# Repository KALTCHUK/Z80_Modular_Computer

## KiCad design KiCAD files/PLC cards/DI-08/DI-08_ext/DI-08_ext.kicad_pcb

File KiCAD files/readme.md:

## What you'll find in this directory ##
The most important here are the two directories called "Proton cards" and "PLC cards", which contain respectively all the cards used in the Proton projects and, all the I/O cards mounted on DIN rail, which communicate with the Proton via Modbus protocol over RS485.

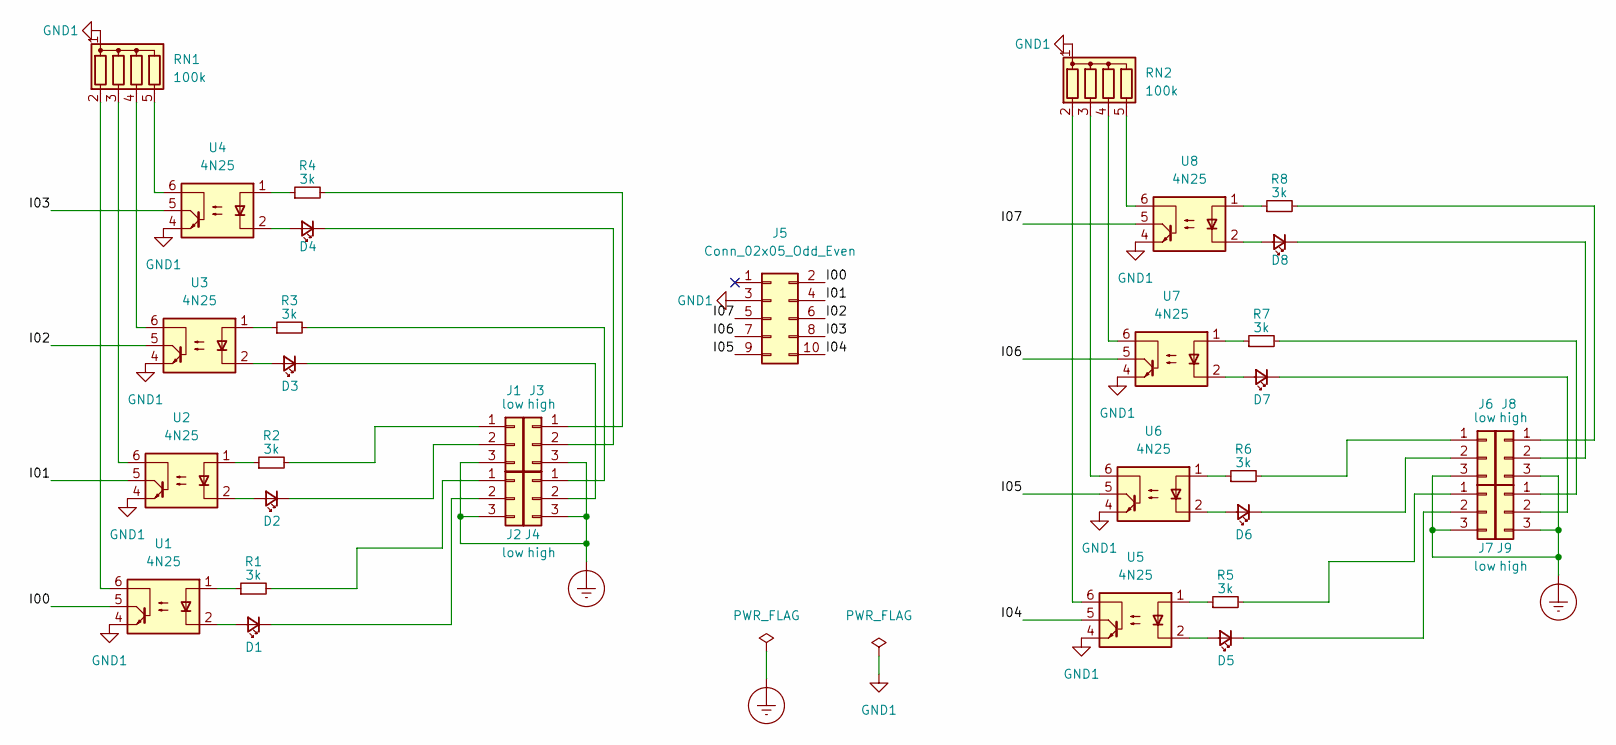
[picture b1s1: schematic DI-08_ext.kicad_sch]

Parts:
D1, D2, D3, D4, D5, D6, D7, D8: LED_Small; LED_D3.0mm
J1, J2, J6, J7: low; PhoenixContact_MSTBVA_2,5_3-G-5,08_1x03_P5.08mm_Vertical
J3, J4, J8, J9: high; PhoenixContact_MSTBVA_2,5_3-G-5,08_1x03_P5.08mm_Vertical
J5: Conn_02x05_Odd_Even; PinSocket_2x05_P2.54mm_Vertical
R1, R2, R3, R4, R5, R6, R7, R8: 3k; R_Axial_DIN0207_L6.3mm_D2.5mm_P2.54mm_Vertical
RN1, RN2: 100k; R_Array_SIP5
U1, U2, U3, U4, U5, U6, U7, U8: 4N25; DIP-6_W7.62mm_Socket_LongPads

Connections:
/I00: J5.2, U1.5
/I01: J5.4, U2.5
/I02: J5.6, U3.5
/I03: J5.8, U4.5
/I04: J5.10, U5.5
/I05: J5.9, U6.5
/I06: J5.7, U7.5
/I07: J5.5, U8.5
Earth_Protective: J1.3, J2.3, J3.3, J4.3, J6.3, J7.3, J8.3, J9.3
GND1: J5.3, RN1.1 (common), RN2.1 (common), U1.4, U2.4, U3.4, U4.4, U5.4, U6.4, U7.4, U8.4
unnamed: D1.1 (K), J2.2
unnamed: D1.2 (A), U1.2
unnamed: D2.1 (K), J1.2
unnamed: D2.2 (A), U2.2
unnamed: D3.1 (K), J4.2
unnamed: D3.2 (A), U3.2
unnamed: D4.1 (K), J3.2
unnamed: D4.2 (A), U4.2
unnamed: D5.1 (K), J7.2
unnamed: D5.2 (A), U5.2
unnamed: D6.1 (K), J6.2
unnamed: D6.2 (A), U6.2
unnamed: D7.1 (K), J9.2
unnamed: D7.2 (A), U7.2
unnamed: D8.1 (K), J8.2
unnamed: D8.2 (A), U8.2
unnamed: J1.1, R2.2
unnamed: J2.1, R1.2
unnamed: J3.1, R4.2
unnamed: J4.1, R3.2
unnamed: J6.1, R6.2
unnamed: J7.1, R5.2
unnamed: J8.1, R8.2
unnamed: J9.1, R7.2
unnamed: R1.1, U1.1
unnamed: R2.1, U2.1
unnamed: R3.1, U3.1
unnamed: R4.1, U4.1
unnamed: R5.1, U5.1
unnamed: R6.1, U6.1
unnamed: R7.1, U7.1
unnamed: R8.1, U8.1
unnamed: RN1.2 (R1), U1.6
unnamed: RN1.3 (R2), U2.6
unnamed: RN1.4 (R3), U3.6
unnamed: RN1.5 (R4), U4.6
unnamed: RN2.2 (R1), U5.6
unnamed: RN2.3 (R2), U6.6
unnamed: RN2.4 (R3), U7.6
unnamed: RN2.5 (R4), U8.6

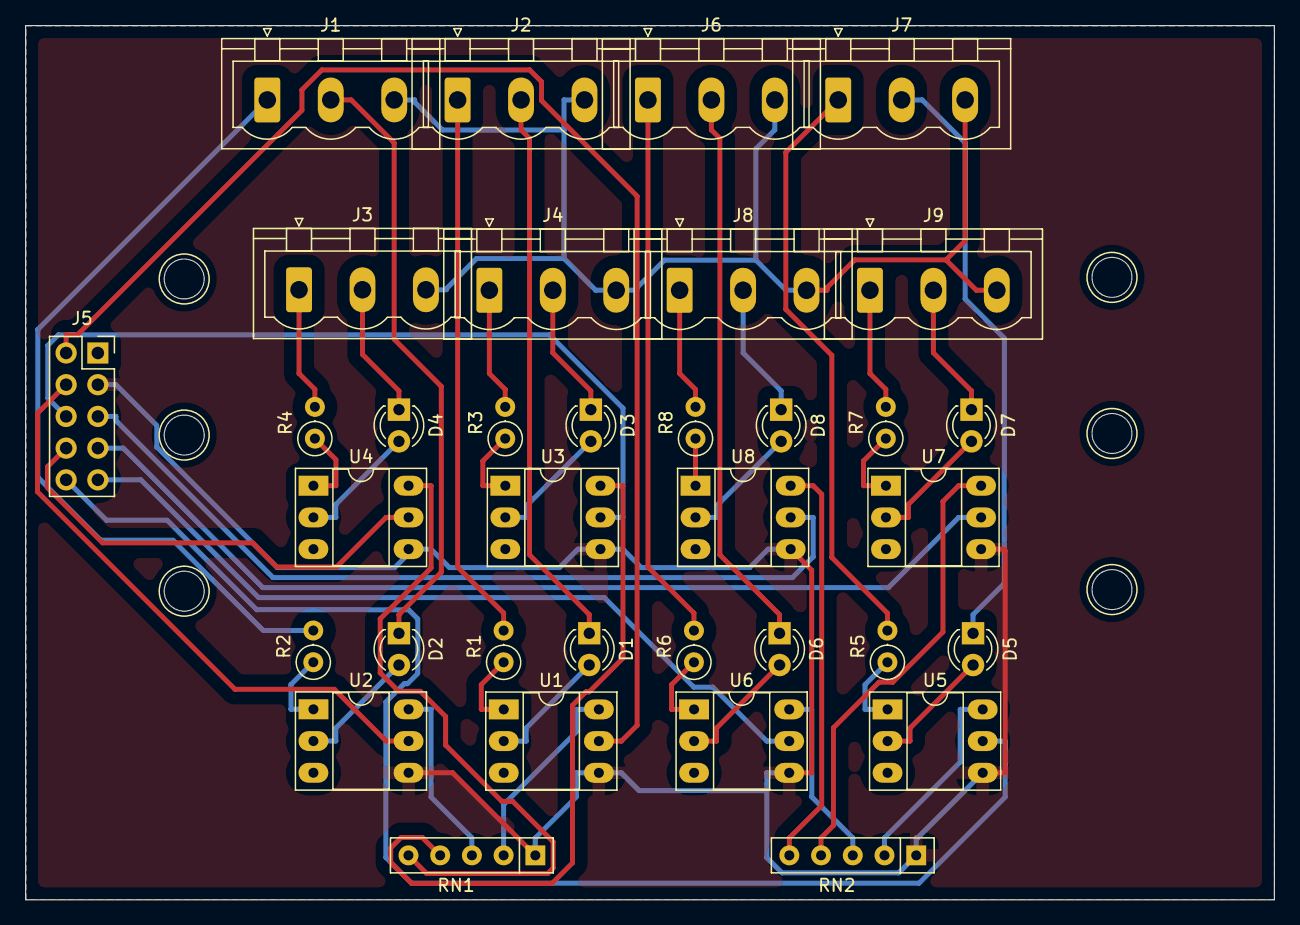
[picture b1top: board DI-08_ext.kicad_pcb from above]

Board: 2 copper layers, 100.0 x 70.0 mm, 37 parts (0 on the bottom side), 50 nets.

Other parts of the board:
DRA1, DRA2: DIN_Rail_Adapter; DINRailAdapter_3xM3_PhoenixContact_1201578

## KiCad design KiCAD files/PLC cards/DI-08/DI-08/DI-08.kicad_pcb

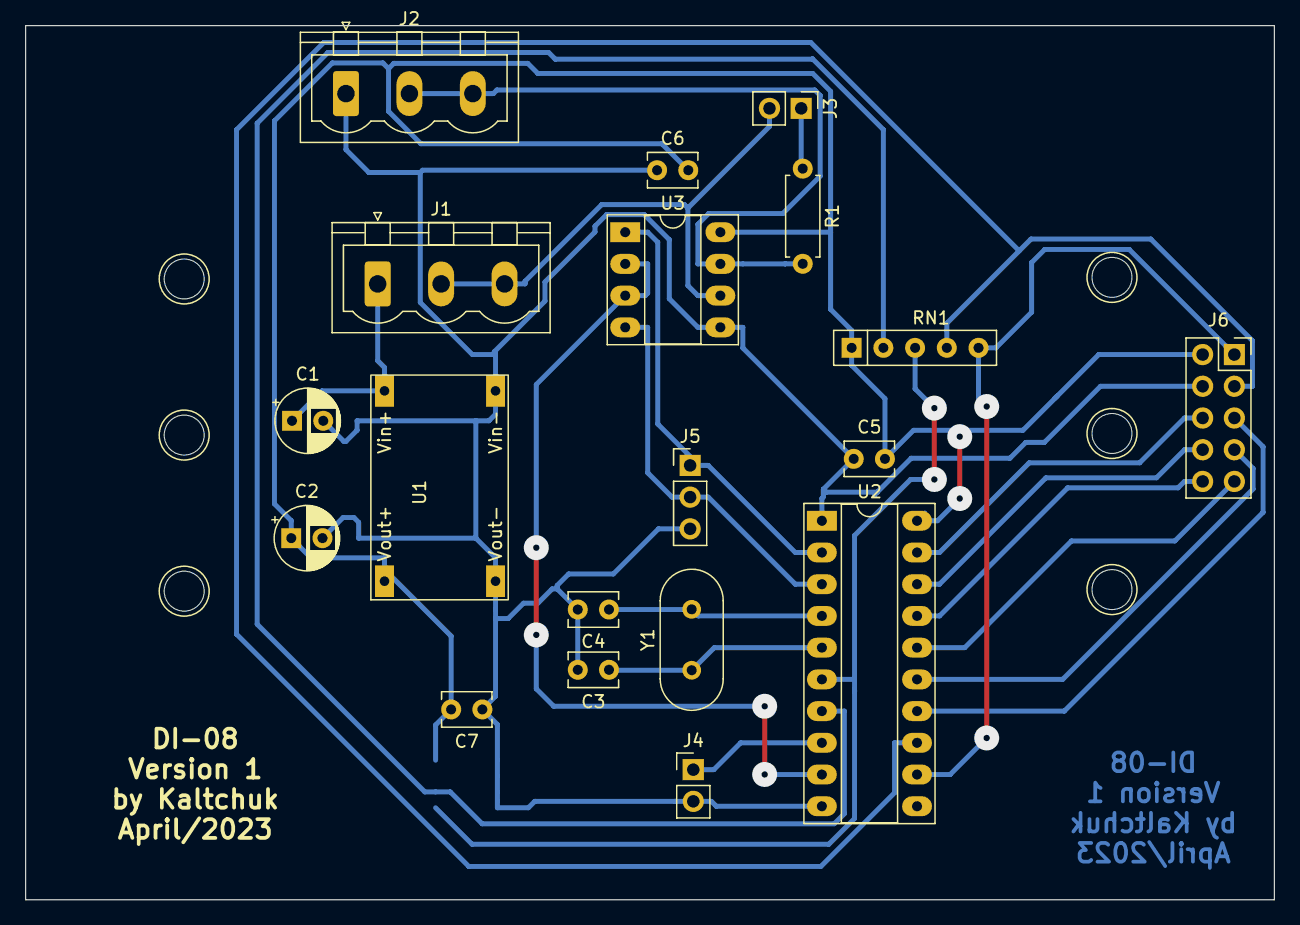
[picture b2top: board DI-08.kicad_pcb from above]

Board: 2 copper layers, 100.0 x 70.0 mm, 22 parts (1 on the bottom side), 22 nets.

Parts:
C1: 47uF; CP_Radial_D5.0mm_P2.50mm
C2: 22uF; CP_Radial_D5.0mm_P2.50mm
C3, C4: 33pF; C_Disc_D3.8mm_W2.6mm_P2.50mm
C5, C6, C7: 10nF; C_Disc_D3.8mm_W2.6mm_P2.50mm
DRA1, DRA2: DIN_Rail_Adapter; DINRailAdapter_3xM3_PhoenixContact_1201578
J1: high; PhoenixContact_MSTBVA_2,5_3-G-5,08_1x03_P5.08mm_Vertical
J2: low; PhoenixContact_MSTBVA_2,5_3-G-5,08_1x03_P5.08mm_Vertical
J3: terminal; PinHeader_1x02_P2.54mm_Vertical
J4: factory setup; PinHeader_1x02_P2.54mm_Vertical
J5: TTL comm; PinHeader_1x03_P2.54mm_Vertical
J6: Bridge_female; PinSocket_2x05_P2.54mm_Vertical
R1: 250; R_Axial_DIN0207_L6.3mm_D2.5mm_P7.62mm_Horizontal
RN1: 10k; R_Array_SIP5
U1: DSN-MINI-360
U2: AT89C4051-24P; DIP-20_W7.62mm_Socket_LongPads
U3: SN75176AP; DIP-8_W7.62mm_Socket_LongPads
U4: FM24C64B; SOIC-8_3.9x4.9mm_P1.27mm
Y1: 11.059MHz; Crystal_HC49-U_Vertical

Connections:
+5V: C2.1, C5.2, C6.2, C7.2, J6.2, RN1.1 (common), U1.1 (Vout+), U2.20 (VCC), U3.8 (VCC), U4.8 (VDD)
+24V: C1.1, J1.1, U1.3 (Vin+)
/DE: U2.9 (P3.5), U3.2 (~RE), U3.3 (DE)
/FS: J4.1, U2.8 (P3.4)
/MB-A: J1.2, J1.3, J3.2, U3.6 (A)
/MB-B: J2.2, J2.3, R1.2, U3.7 (B)
/RX: J5.1, U2.2 (P3.0), U3.1 (R)
/SCL: RN1.2 (R1), U2.7 (P3.3), U4.6 (SCL)
/SDA: RN1.3 (R2), U2.6 (P3.2), U4.5 (SDA)
/TX: J5.2, U2.3 (P3.1), U3.4 (D)
GND: C1.2, C2.2, C3.2, C4.2, C5.1, C6.1, C7.1, J2.1, J4.2, J5.3, J6.4, U1.2 (Vout-), U1.4 (Vin-), U2.1 (RST/VPP), U2.10 (GND), U3.5 (GND), U4.1 (A0), U4.2 (A1), U4.3 (A2), U4.4 (VSS)
unnamed: C3.1, U2.5 (XTAL1), Y1.1
unnamed: C4.1, U2.4 (XTAL2), Y1.2
unnamed: J3.1, R1.1
unnamed: J6.1, RN1.5 (R4), U2.12 (P1.0)
unnamed: J6.3, RN1.4 (R3), U2.13 (P1.1)
unnamed: J6.5, U2.14 (P1.2)
unnamed: J6.6, U2.19 (P1.7)
unnamed: J6.7, U2.15 (P1.3)
unnamed: J6.8, U2.18 (P1.6)
unnamed: J6.9, U2.16 (P1.4)
unnamed: J6.10, U2.17 (P1.5)

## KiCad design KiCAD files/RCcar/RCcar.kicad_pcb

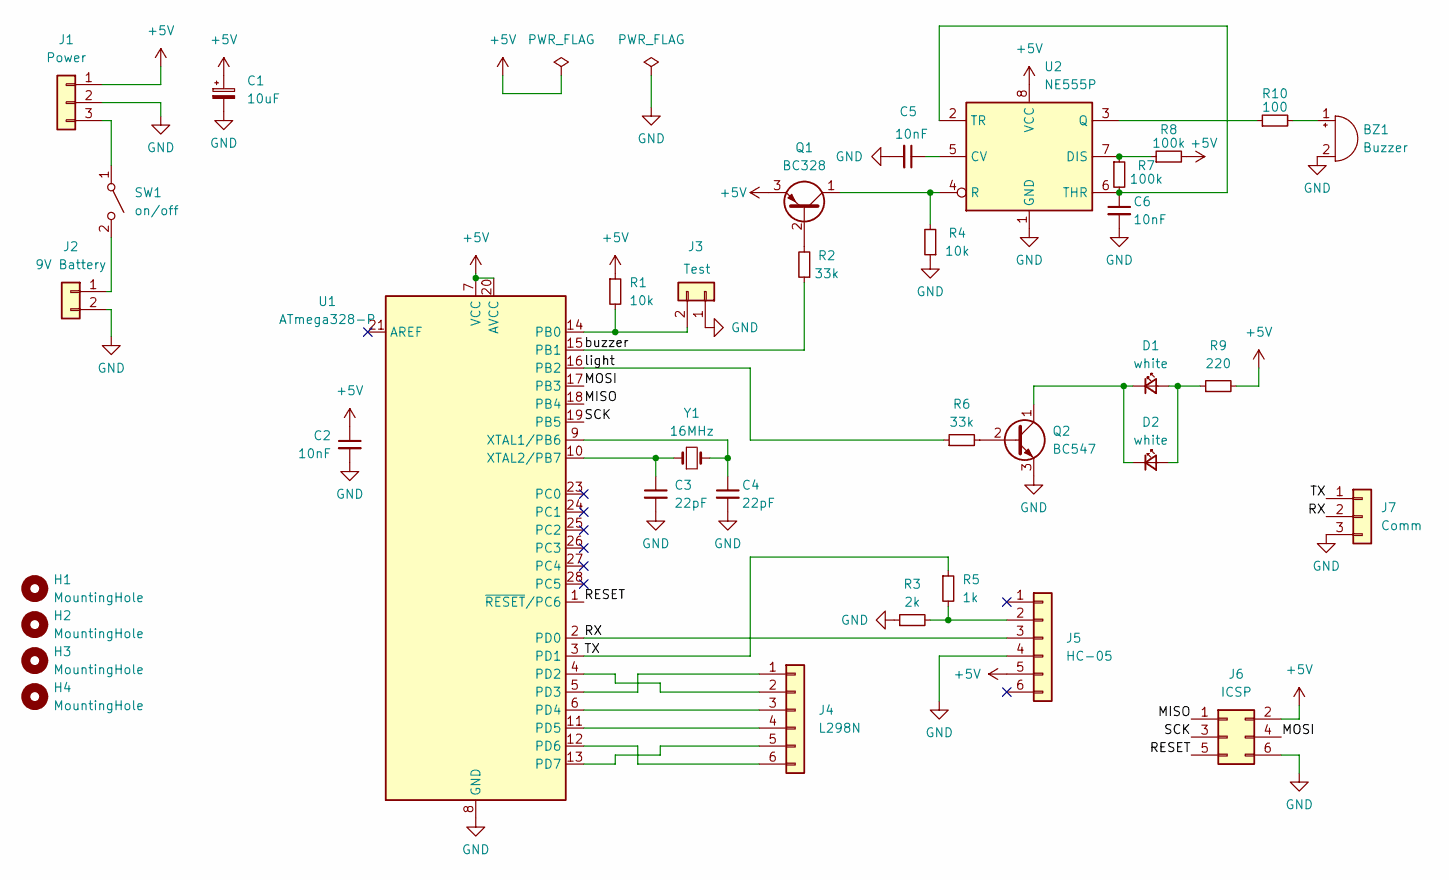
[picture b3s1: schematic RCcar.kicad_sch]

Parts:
BZ1: Buzzer; Buzzer_12x9.5RM7.6
C1: 10uF; CP_Radial_D5.0mm_P2.50mm
C2, C5, C6: 10nF; C_Disc_D3.0mm_W2.0mm_P2.50mm
C3, C4: 22pF; C_Disc_D3.0mm_W2.0mm_P2.50mm
D1, D2: white; LED_D3.0mm_Clear
H1, H2, H3, H4: MountingHole; MountingHole_3mm
J1: Power; PinHeader_1x03_P2.54mm_Vertical
J2: 9V Battery; PinHeader_1x02_P2.54mm_Vertical
J3: Test; PinHeader_1x02_P2.54mm_Vertical
J4: L298N; PinHeader_1x06_P2.54mm_Vertical
J5: HC-05; PinSocket_1x06_P2.54mm_Vertical
J6: ICSP; PinHeader_2x03_P2.54mm_Vertical
J7: Comm; PinHeader_1x03_P2.54mm_Vertical
Q1: BC328; TO-92_Inline
Q2: BC547; TO-92_Inline
R1, R4: 10k; R_Axial_DIN0207_L6.3mm_D2.5mm_P7.62mm_Horizontal
R2, R6: 33k; R_Axial_DIN0207_L6.3mm_D2.5mm_P7.62mm_Horizontal
R3: 2k; R_Axial_DIN0207_L6.3mm_D2.5mm_P7.62mm_Horizontal
R5: 1k; R_Axial_DIN0207_L6.3mm_D2.5mm_P7.62mm_Horizontal
R7, R8: 100k; R_Axial_DIN0207_L6.3mm_D2.5mm_P7.62mm_Horizontal
R9: 220; R_Axial_DIN0207_L6.3mm_D2.5mm_P7.62mm_Horizontal
R10: 100; R_Axial_DIN0207_L6.3mm_D2.5mm_P7.62mm_Horizontal
SW1: on/off; SW_CW_GPTS203211B
U1: ATmega328-P; DIP-28_W7.62mm_Socket_LongPads
U2: NE555P; DIP-8_W7.62mm_Socket_LongPads
Y1: 16MHz; Crystal_HC49-4H_Vertical

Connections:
+5V: C1.1, C2.1, J1.1, J5.5, J6.2, Q1.3 (E), R1.1, R8.2, R9.2, U1.7 (VCC), U1.20 (AVCC), U2.8 (VCC)
/MISO: J6.1, U1.18 (PB4)
/MOSI: J6.4, U1.17 (PB3)
/RESET: J6.5, U1.1 (~RESET/PC6)
/RX: J5.3, J7.2, U1.2 (PD0)
/SCK: J6.3, U1.19 (PB5)
/TX: J7.1, R5.1, U1.3 (PD1)
/buzzer: R2.1, U1.15 (PB1)
/light: R6.1, U1.16 (PB2)
GND: BZ1.2 (+), C1.2, C2.2, C3.2, C4.2, C5.2, C6.2, J1.2, J2.2, J3.1, J5.4, J6.6, J7.3, Q2.3 (E), R3.1, R4.1, U1.8 (GND), U1.22 (GND), U2.1 (GND)
unnamed: BZ1.1 (-), R10.2
unnamed: C3.1, U1.10 (XTAL2/PB7), Y1.1
unnamed: C4.1, U1.9 (XTAL1/PB6), Y1.2
unnamed: C5.1, U2.5 (CV)
unnamed: C6.1, R7.2, U2.2 (TR), U2.6 (THR)
unnamed: D1.1 (K), D2.1 (K), Q2.1 (C)
unnamed: D1.2 (A), D2.2 (A), R9.1
unnamed: J1.3, SW1.1 (A)
unnamed: J2.1, SW1.2 (B)
unnamed: J3.2, R1.2, U1.14 (PB0)
unnamed: J4.1, U1.5 (PD3)
unnamed: J4.2, U1.4 (PD2)
unnamed: J4.3, U1.6 (PD4)
unnamed: J4.4, U1.11 (PD5)
unnamed: J4.5, U1.13 (PD7)
unnamed: J4.6, U1.12 (PD6)
unnamed: J5.2, R3.2, R5.2
unnamed: Q1.1 (C), R4.2, U2.4 (R)
unnamed: Q1.2 (B), R2.2
unnamed: Q2.2 (B), R6.2
unnamed: R7.1, R8.1, U2.7 (DIS)
unnamed: R10.1, U2.3 (Q)

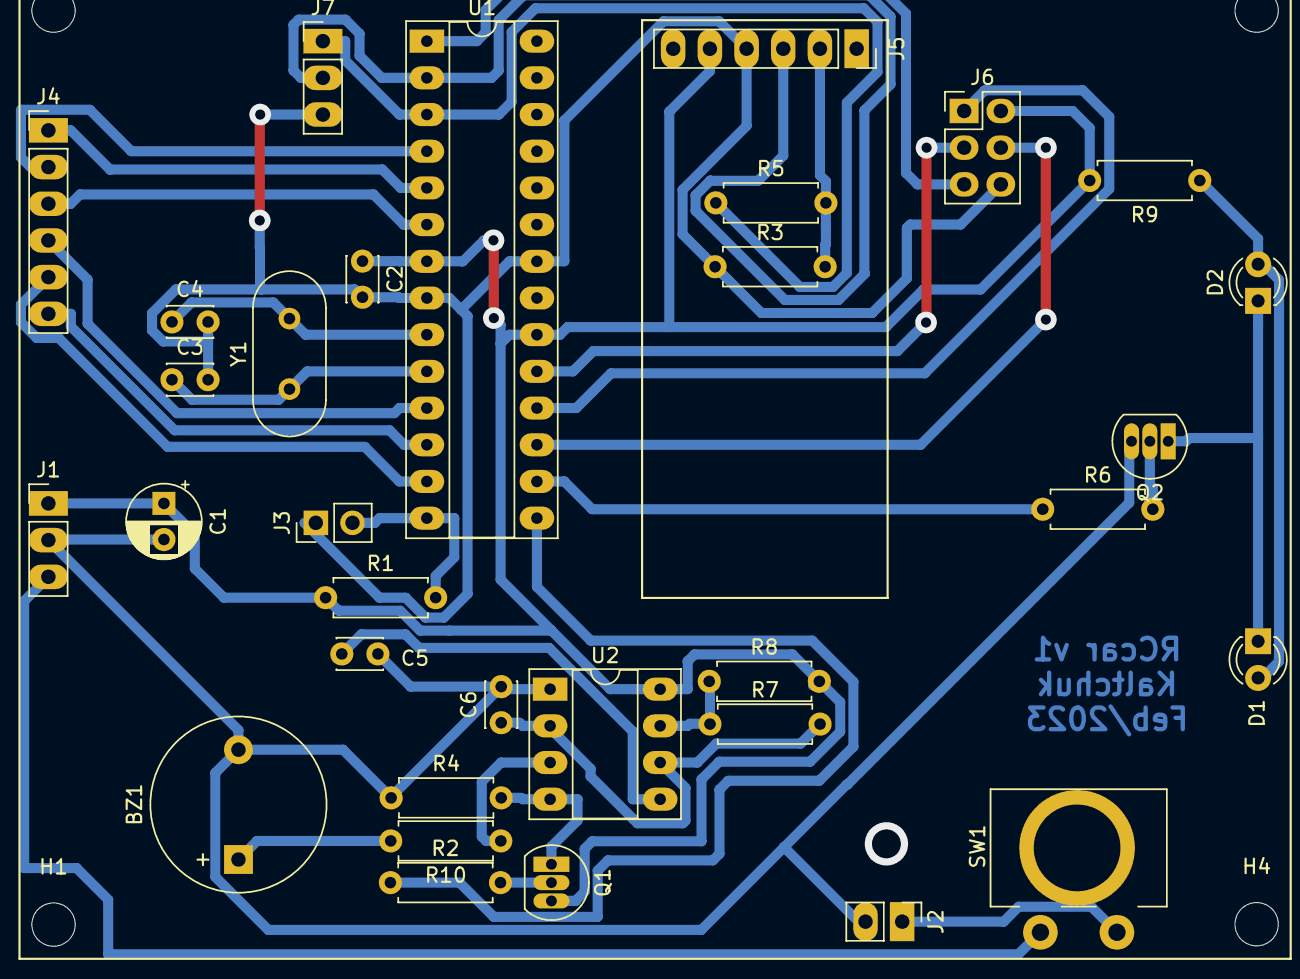
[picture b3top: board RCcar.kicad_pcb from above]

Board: 2 copper layers, 36 parts (0 on the bottom side), 32 nets.

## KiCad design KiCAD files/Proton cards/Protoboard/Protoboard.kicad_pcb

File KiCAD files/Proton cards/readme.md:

## What you'll find in this directory ##
Each subdirectory contains the KiCAD files for a specific Proton card, assembled in the rack. They all contain the circuit diagrams. Most of them also have the PCB layouts and some even have the Gerber files I sent to the PCB manufacturers (PCBway and JLC PCB)).

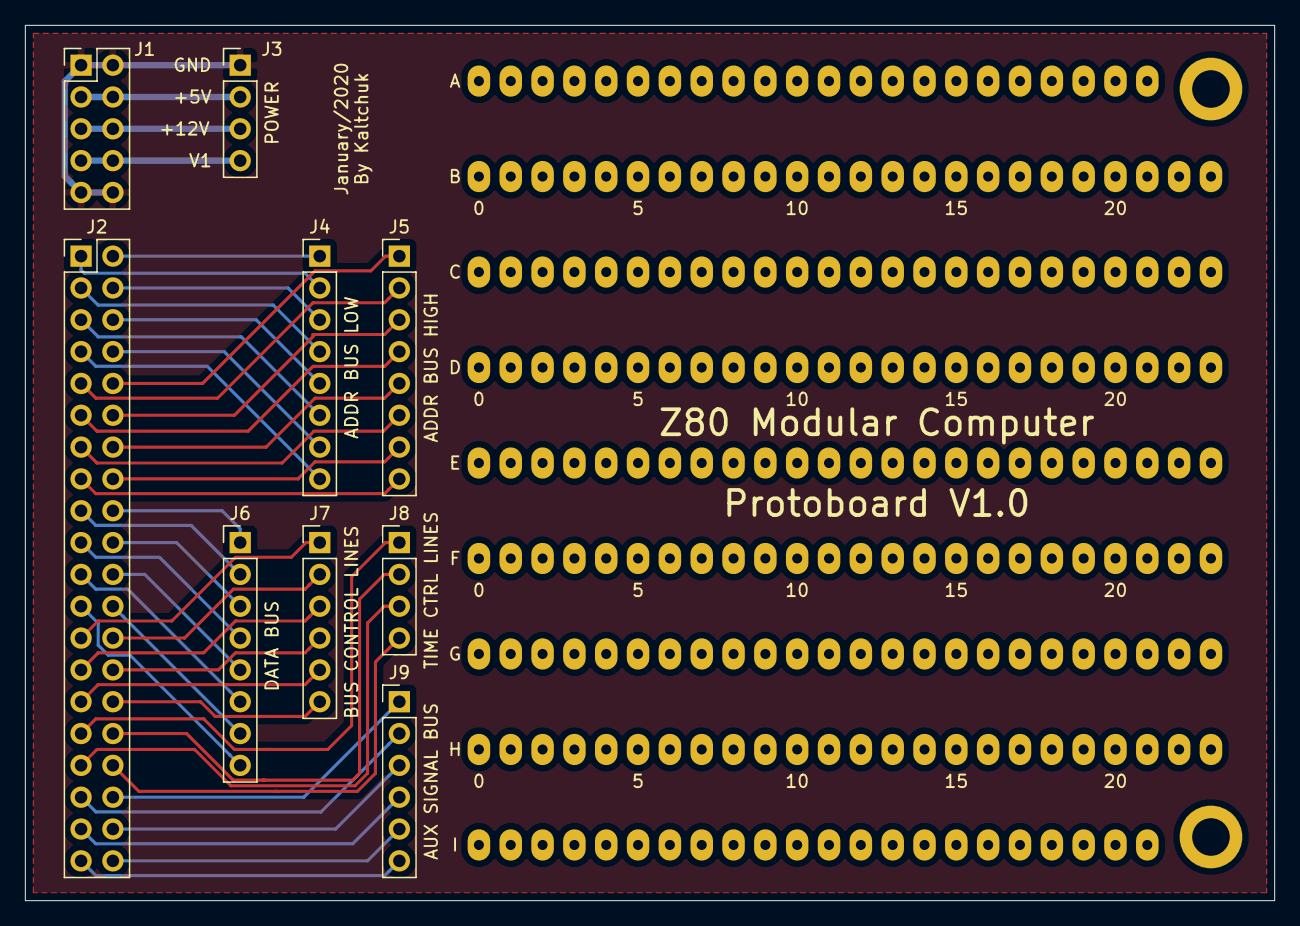
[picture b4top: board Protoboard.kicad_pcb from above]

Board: 2 copper layers, 99.7 x 69.8 mm, 9 parts (0 on the bottom side), 44 nets.

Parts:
J1: Conn_02x05; PinHeader_2x05_P2.54mm_Vertical
J2: Conn_02x20; PinHeader_2x20_P2.54mm_Vertical
J3, J8: Conn_01x04; PinHeader_1x04_P2.54mm_Vertical
J4, J5, J6: Conn_01x08; PinHeader_1x08_P2.54mm_Vertical
J7, J9: Conn_01x06; PinHeader_1x06_P2.54mm_Vertical

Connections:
/+5V: J1.3, J1.4, J3.2
/+12V: J1.5, J1.6, J3.3
/a00: J2.2, J4.1
/a01: J2.1, J4.2
/a02: J2.4, J4.3
/a03: J2.3, J4.4
/a04: J2.6, J4.5
/a05: J2.5, J4.6
/a06: J2.8, J4.7
/a07: J2.7, J4.8
/a08: J2.10, J5.1
/a09: J2.9, J5.2
/a10: J2.12, J5.3
/a11: J2.11, J5.4
/a12: J2.14, J5.5
/a13: J2.13, J5.6
/a14: J2.16, J5.7
/a15: J2.15, J5.8
/busack: J2.29, J7.5
/busrq: J2.30, J7.6
/clk: J2.39, J9.6
/d00: J2.18, J6.1
/d01: J2.17, J6.2
/d02: J2.20, J6.3
/d03: J2.19, J6.4
/d04: J2.22, J6.5
/d05: J2.21, J6.6
/d06: J2.24, J6.7
/d07: J2.23, J6.8
/gnd: J1.1, J1.2, J1.9, J1.10, J3.1
/halt: J2.31, J8.1
/int: J2.33, J8.3
/iorq: J2.28, J7.4
/m1: J2.37, J9.4
/mreq: J2.26, J7.2
/nmi: J2.34, J8.4
/rd: J2.27, J7.3
/reset: J2.40, J9.5
/rfsh: J2.38, J9.3
/s0: J2.36, J9.1
/s1: J2.35, J9.2
/v1: J1.7, J1.8, J3.4
/wait: J2.32, J8.2
/wr: J2.25, J7.1

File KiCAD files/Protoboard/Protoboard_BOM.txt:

J1	Power Bus	Connector_PinHeader_2.54mm:PinHeader_2x05_P2.54mm_Vertical	~	1
    J2	Signal Bus	Connector_PinHeader_2.54mm:PinHeader_2x20_P2.54mm_Vertical	~	1
    J3	Power	Connector_PinHeader_2.54mm:PinHeader_1x04_P2.54mm_Vertical	~	1
    J4	ADDR LO	Connector_PinHeader_2.54mm:PinHeader_1x08_P2.54mm_Vertical	~	1
    J5	ADDR HI	Connector_PinHeader_2.54mm:PinHeader_1x08_P2.54mm_Vertical	~	1
    J6	DATA	Connector_PinHeader_2.54mm:PinHeader_1x08_P2.54mm_Vertical	~	1
    J7	BUS CTRL	Connector_PinHeader_2.54mm:PinHeader_1x06_P2.54mm_Vertical	~	1
    J8	TIME CTRL	Connector_PinHeader_2.54mm:PinHeader_1x04_P2.54mm_Vertical	~	1
    J9	AUX SIGNAL	Connector_PinHeader_2.54mm:PinHeader_1x06_P2.54mm_Vertical	~	1

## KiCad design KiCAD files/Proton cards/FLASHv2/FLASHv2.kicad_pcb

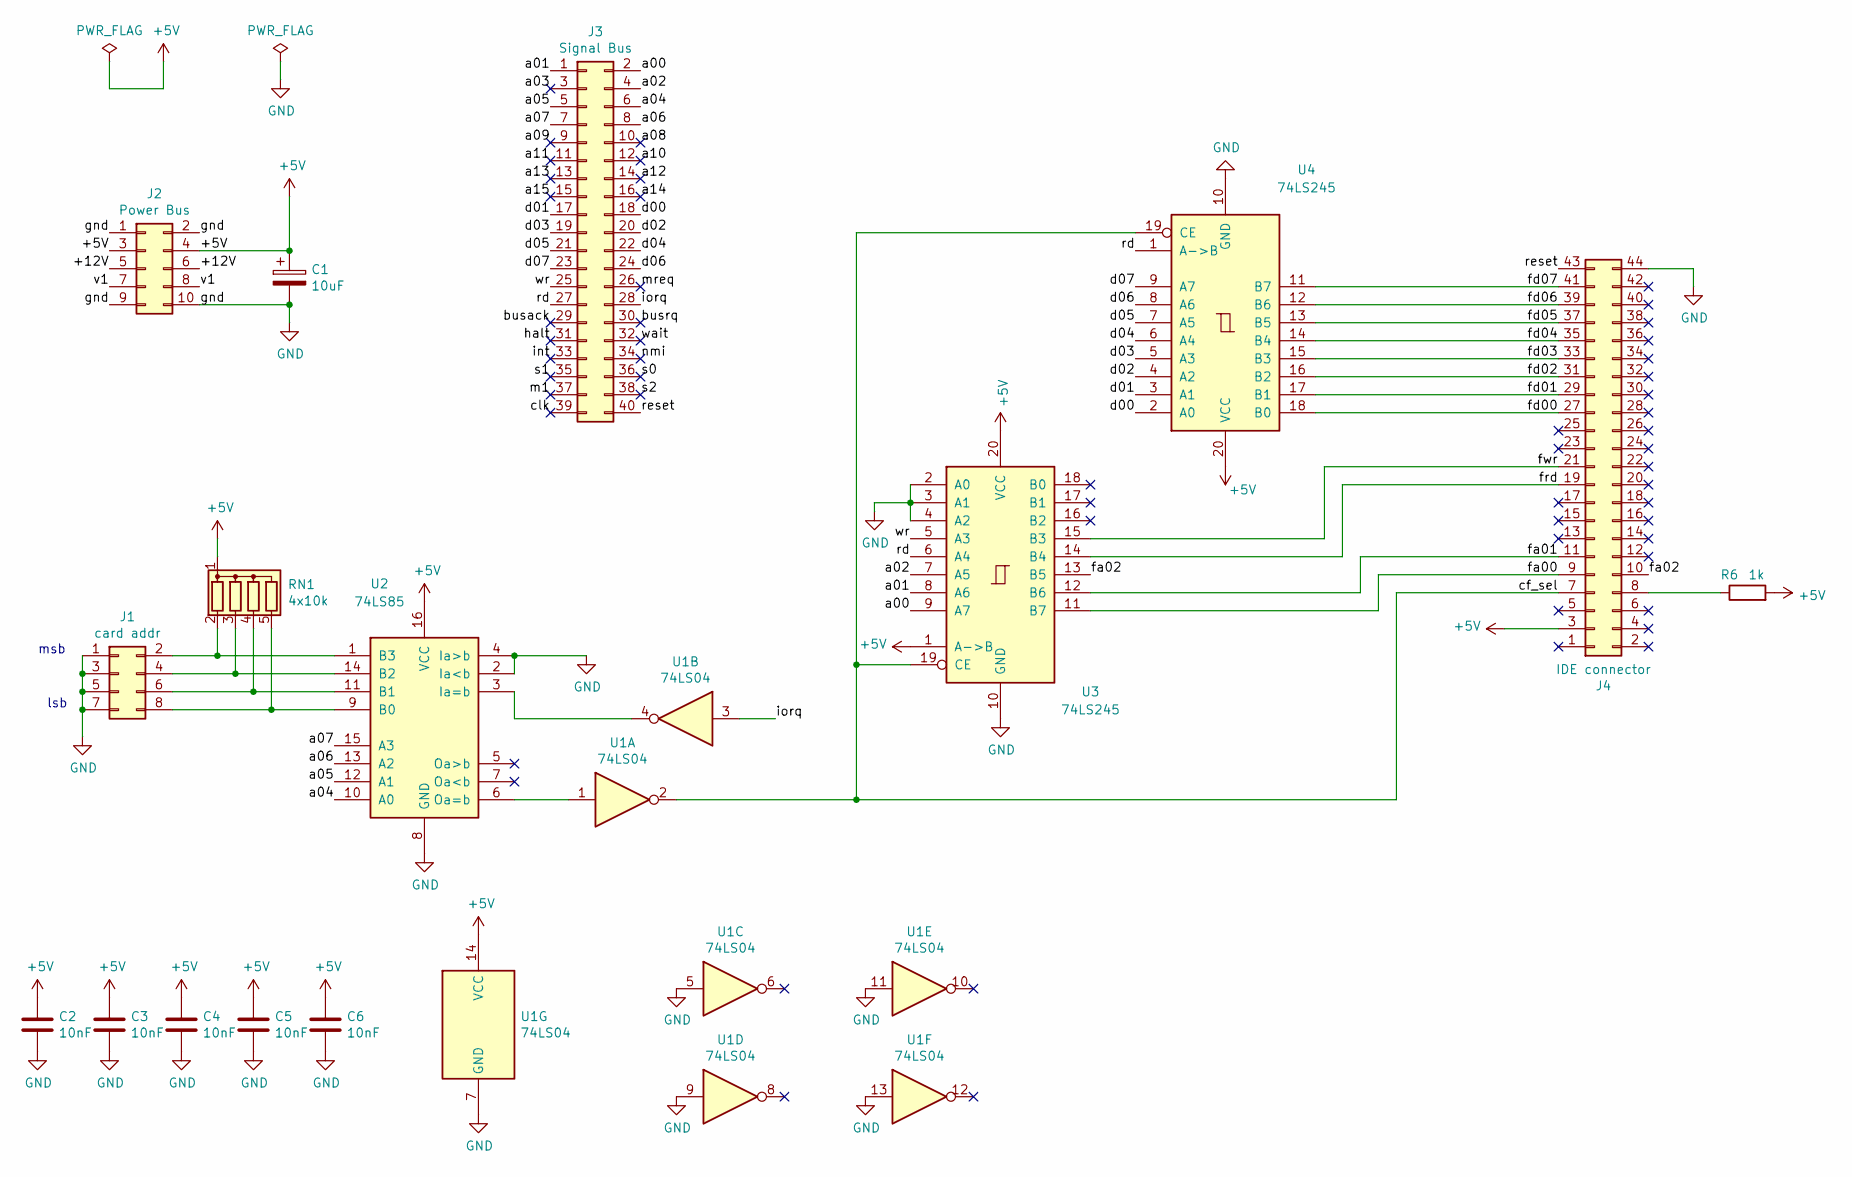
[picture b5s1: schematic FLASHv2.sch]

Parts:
C1: 10uF; CP_Radial_D5.0mm_P2.50mm
C2, C3, C4, C5, C6: 10nF; C_Disc_D3.8mm_W2.6mm_P2.50mm
J1: card addr; PinHeader_2x04_P2.54mm_Vertical
J2: Power Bus; PinHeader_2x05_P2.54mm_Vertical
J3: Signal Bus; PinHeader_2x20_P2.54mm_Vertical
J4: IDE connector; PinHeader_2x22_P2.00mm_Vertical
R6: 1k; R_Axial_DIN0207_L6.3mm_D2.5mm_P10.16mm_Horizontal
RN1: 4x10k; R_Array_SIP5
U1: 74LS04; DIP-14_W7.62mm_Socket_LongPads
U2: 74LS85; DIP-16_W7.62mm_Socket_LongPads
U3, U4: 74LS245; DIP-20_W7.62mm_Socket_LongPads

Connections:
+5V: C1.1, C2.1, C3.1, C4.1, C5.1, C6.1, J2.3, J2.4, J4.3, R6.2, RN1.1 (common), U1.14 (VCC), U2.16 (VCC), U3.1 (A->B), U3.20 (VCC), U4.20 (VCC)
/+12V: J2.5, J2.6
/a00: J3.2, U3.9 (A7)
/a01: J3.1, U3.8 (A6)
/a02: J3.4, U3.7 (A5)
/a03: J3.3
/a04: J3.6, U2.10 (A0)
/a05: J3.5, U2.12 (A1)
/a06: J3.8, U2.13 (A2)
/a07: J3.7, U2.15 (A3)
/a08: J3.10
/a09: J3.9
/a10: J3.12
/a11: J3.11
/a12: J3.14
/a13: J3.13
/a14: J3.16
/a15: J3.15
/busack: J3.29
/busrq: J3.30
/cf_sel: J4.7, U1.2, U3.19 (CE), U4.19 (CE)
/clk: J3.39
/d00: J3.18, U4.2 (A0)
/d01: J3.17, U4.3 (A1)
/d02: J3.20, U4.4 (A2)
/d03: J3.19, U4.5 (A3)
/d04: J3.22, U4.6 (A4)
/d05: J3.21, U4.7 (A5)
/d06: J3.24, U4.8 (A6)
/d07: J3.23, U4.9 (A7)
/fa00: J4.9, U3.11 (B7)
/fa01: J4.11, U3.12 (B6)
/fa02: J4.10, U3.13 (B5)
/fd00: J4.27, U4.18 (B0)
/fd01: J4.29, U4.17 (B1)
/fd02: J4.31, U4.16 (B2)
/fd03: J4.33, U4.15 (B3)
/fd04: J4.35, U4.14 (B4)
/fd05: J4.37, U4.13 (B5)
/fd06: J4.39, U4.12 (B6)
/fd07: J4.41, U4.11 (B7)
/frd: J4.19, U3.14 (B4)
/fwr: J4.21, U3.15 (B3)
/halt: J3.31
/int: J3.33
/iorq: J3.28, U1.3
/m1: J3.37
/mreq: J3.26
/nmi: J3.34
/rd: J3.27, U3.6 (A4), U4.1 (A->B)
/reset: J3.40, J4.43
/s0: J3.36
/s1: J3.35
/s2: J3.38
/v1: J2.7, J2.8
/wait: J3.32
/wr: J3.25, U3.5 (A3)
GND: C1.2, C2.2, C3.2, C4.2, C5.2, C6.2, J1.1, J1.3, J1.5, J1.7, J2.1, J2.2, J2.9, J2.10, J4.44, U1.5, U1.7 (GND), U1.9, U1.11, U1.13, U2.2 (Ia<b), U2.4 (Ia>b), U2.8 (GND), U3.2 (A0), U3.3 (A1), U3.4 (A2), U3.10 (GND), U4.10 (GND)
unnamed: J1.2, RN1.2 (R1), U2.1 (B3)
unnamed: J1.4, RN1.3 (R2), U2.14 (B2)
unnamed: J1.6, RN1.4 (R3), U2.11 (B1)
unnamed: J1.8, RN1.5 (R4), U2.9 (B0)
unnamed: J4.8, R6.1
unnamed: U1.1, U2.6 (Oa=b)
unnamed: U1.4, U2.3 (Ia=b)

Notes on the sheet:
msb
lsb

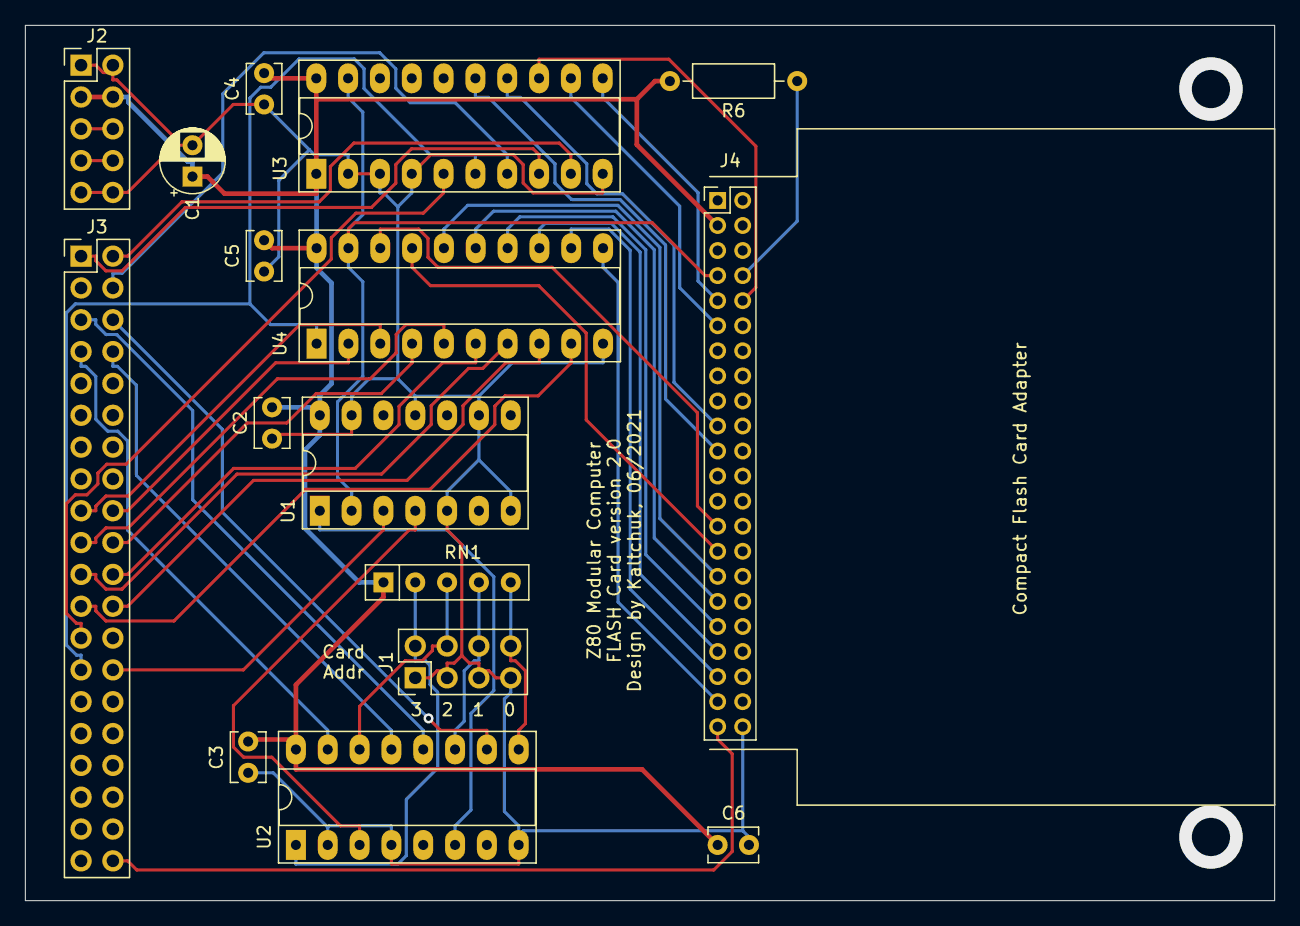
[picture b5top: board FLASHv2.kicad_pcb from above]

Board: 2 copper layers, 99.7 x 69.8 mm, 16 parts (0 on the bottom side), 44 nets.

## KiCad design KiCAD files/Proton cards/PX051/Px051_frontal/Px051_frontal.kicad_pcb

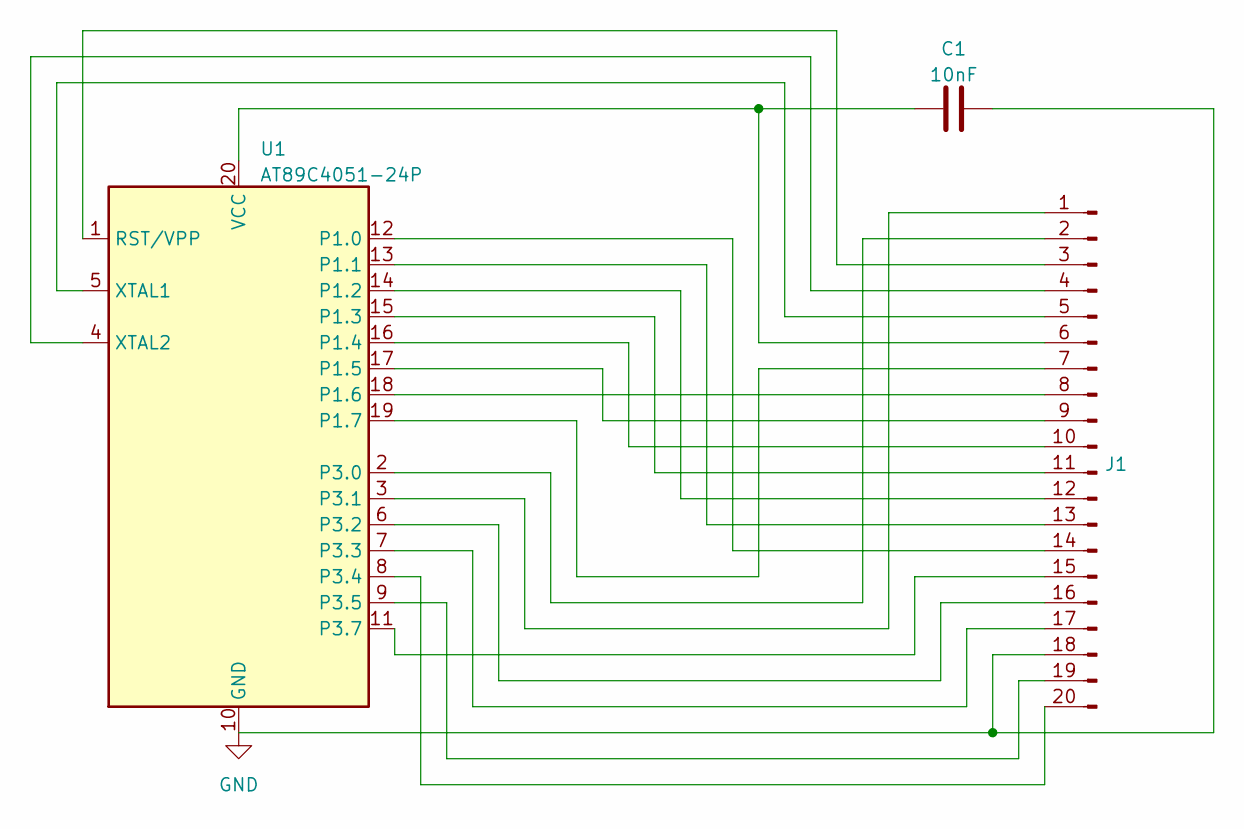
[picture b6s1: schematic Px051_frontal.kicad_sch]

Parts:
C1: 10nF; C_Disc_D3.0mm_W2.0mm_P2.50mm
J1: Conn_01x20_Male; PinHeader_1x20_P2.54mm_Vertical
U1: AT89C4051-24P; DIP-20_W7.62mm_Socket_LongPads

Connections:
GND: C1.2, J1.18, U1.10 (GND)
unnamed: C1.1, J1.6, U1.20 (VCC)
unnamed: J1.1, U1.3 (P3.1)
unnamed: J1.2, U1.2 (P3.0)
unnamed: J1.3, U1.1 (RST/VPP)
unnamed: J1.4, U1.4 (XTAL2)
unnamed: J1.5, U1.5 (XTAL1)
unnamed: J1.7, U1.19 (P1.7)
unnamed: J1.8, U1.18 (P1.6)
unnamed: J1.9, U1.17 (P1.5)
unnamed: J1.10, U1.16 (P1.4)
unnamed: J1.11, U1.15 (P1.3)
unnamed: J1.12, U1.14 (P1.2)
unnamed: J1.13, U1.13 (P1.1)
unnamed: J1.14, U1.12 (P1.0)
unnamed: J1.15, U1.11 (P3.7)
unnamed: J1.16, U1.6 (P3.2)
unnamed: J1.17, U1.7 (P3.3)
unnamed: J1.19, U1.9 (P3.5)
unnamed: J1.20, U1.8 (P3.4)

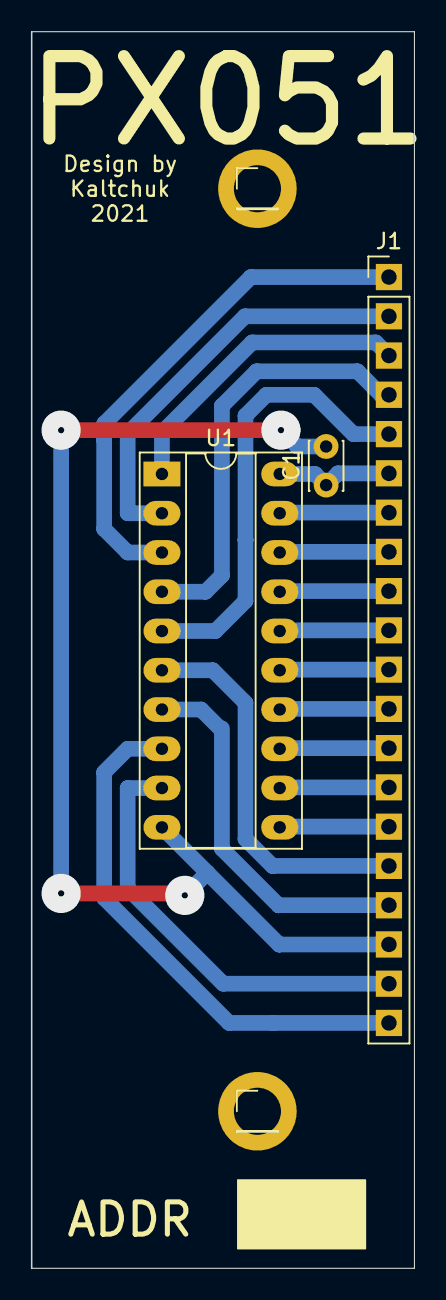
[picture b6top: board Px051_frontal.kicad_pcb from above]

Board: 2 copper layers, 24.8 x 80.0 mm, 5 parts (0 on the bottom side), 20 nets.

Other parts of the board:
J7, J8: fixing bolt; PinHeader_1x01_P2.54mm_Vertical

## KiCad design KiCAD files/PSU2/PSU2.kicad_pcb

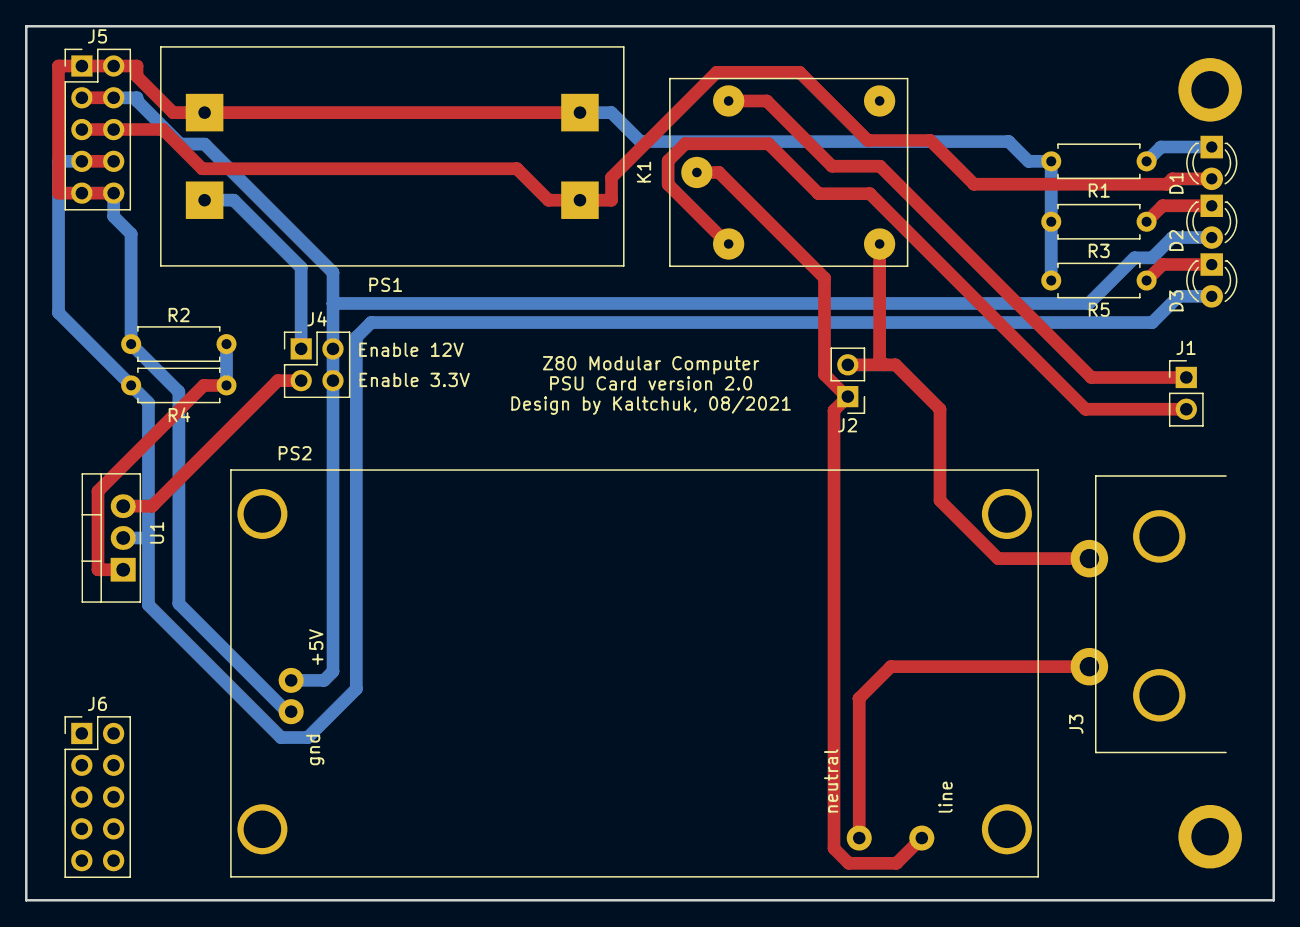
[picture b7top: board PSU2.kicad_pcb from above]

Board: 2 copper layers, 99.7 x 69.8 mm, 20 parts (0 on the bottom side), 15 nets.

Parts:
D1, D2, D3: LED; LED_D3.0mm
H1, H2: MountingHole; Mounting_Hole_0.2in
J1: Ext switch; PinHeader_1x02_P2.54mm_Vertical
J2: To switch; PinHeader_1x02_P2.54mm_Vertical
J3: Mains; IEC60320_2pin
J4: Vo enable; PinHeader_2x02_P2.54mm_Vertical
J5: Power bus; PinHeader_2x05_P2.54mm_Vertical
J6: Mech support; PinHeader_2x05_P2.54mm_Vertical
K1: SRD-05VDC-SL-C; Relay_SPDT_Songel-15x19mm
PS1: MT3608_2-24V_2A
PS2: XPJ-01B_5V_10W; Converter_ACDC_5V_10W_XPJ-01B
R1: 1k2; R_Axial_DIN0207_L6.3mm_D2.5mm_P7.62mm_Horizontal
R2: 390; R_Axial_DIN0207_L6.3mm_D2.5mm_P7.62mm_Horizontal
R3: 330; R_Axial_DIN0207_L6.3mm_D2.5mm_P7.62mm_Horizontal
R4: 240; R_Axial_DIN0207_L6.3mm_D2.5mm_P7.62mm_Horizontal
R5: 150; R_Axial_DIN0207_L6.3mm_D2.5mm_P7.62mm_Horizontal
U1: LM317_TO-220; TO-220-3_Vertical

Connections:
/+3.3V: D3.2 (A), J5.7, J5.8, R4.1, U1.2 (VO)
/+5V: D2.2 (A), J4.2, J4.4, J5.3, J5.4, PS2.4 (+Vo)
/+12V: D1.2 (A), J5.5, J5.6, PS1.4 (+Vout)
GND: J5.1, J5.2, J5.9, J5.10, PS1.1 (-Vin), PS1.3 (-Vout), PS2.3 (-Vo), R1.2, R2.2, R3.2, R5.2
LINE: J2.2, J3.1, K1.1
NEUT: J3.2, PS2.1 (AC/N)
unnamed: D1.1 (K), R1.1
unnamed: D2.1 (K), R3.1
unnamed: D3.1 (K), R5.1
unnamed: J1.1, K1.4
unnamed: J1.2, K1.3
unnamed: J2.1, K1.5, PS2.2 (AC/L)
unnamed: J4.1, PS1.2 (+Vin)
unnamed: J4.3, U1.3 (VI)
unnamed: R2.1, R4.2, U1.1 (ADJ)

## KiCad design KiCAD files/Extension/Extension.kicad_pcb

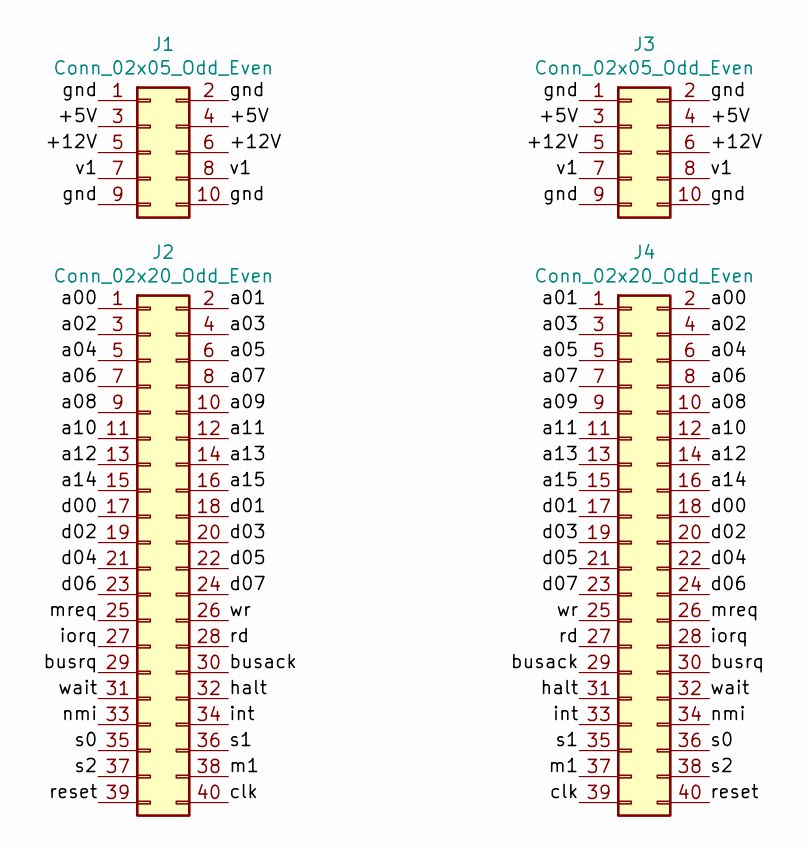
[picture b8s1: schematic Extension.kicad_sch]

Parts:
J1, J3: Conn_02x05_Odd_Even
J2, J4: Conn_02x20_Odd_Even

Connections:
/+5V: J1.3, J1.4, J3.3, J3.4
/+12V: J1.5, J1.6, J3.5, J3.6
/a00: J2.1, J4.2
/a01: J2.2, J4.1
/a02: J2.3, J4.4
/a03: J2.4, J4.3
/a04: J2.5, J4.6
/a05: J2.6, J4.5
/a06: J2.7, J4.8
/a07: J2.8, J4.7
/a08: J2.9, J4.10
/a09: J2.10, J4.9
/a10: J2.11, J4.12
/a11: J2.12, J4.11
/a12: J2.13, J4.14
/a13: J2.14, J4.13
/a14: J2.15, J4.16
/a15: J2.16, J4.15
/busack: J2.30, J4.29
/busrq: J2.29, J4.30
/clk: J2.40, J4.39
/d00: J2.17, J4.18
/d01: J2.18, J4.17
/d02: J2.19, J4.20
/d03: J2.20, J4.19
/d04: J2.21, J4.22
/d05: J2.22, J4.21
/d06: J2.23, J4.24
/d07: J2.24, J4.23
/gnd: J1.1, J1.2, J1.9, J1.10, J3.1, J3.2, J3.9, J3.10
/halt: J2.32, J4.31
/int: J2.34, J4.33
/iorq: J2.27, J4.28
/m1: J2.38, J4.37
/mreq: J2.25, J4.26
/nmi: J2.33, J4.34
/rd: J2.28, J4.27
/reset: J2.39, J4.40
/s0: J2.35, J4.36
/s1: J2.36, J4.35
/s2: J2.37, J4.38
/v1: J1.7, J1.8, J3.7, J3.8
/wait: J2.31, J4.32
/wr: J2.26, J4.25
